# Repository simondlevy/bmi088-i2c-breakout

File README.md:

# BMI088 I^2 Breakout
Tiny I<sup>2</sup>C breakout board for the Bosch BMI088 Inertial Measurement Unit.  Available at tindie.com in 
[standard through-hole](https://www.tindie.com/products/bobbiebots/bmi088-i2c-breakout/) and 
[castellated](https://www.tindie.com/products/bobbiebots/bmi088-i2c-breakout-castellated-pin-version/) versions.

Arduino library [here](https://github.com/simondlevy/bmi088-arduino).

Based on https://github.com/AeroStrike/BMI088-Breakout-Board.

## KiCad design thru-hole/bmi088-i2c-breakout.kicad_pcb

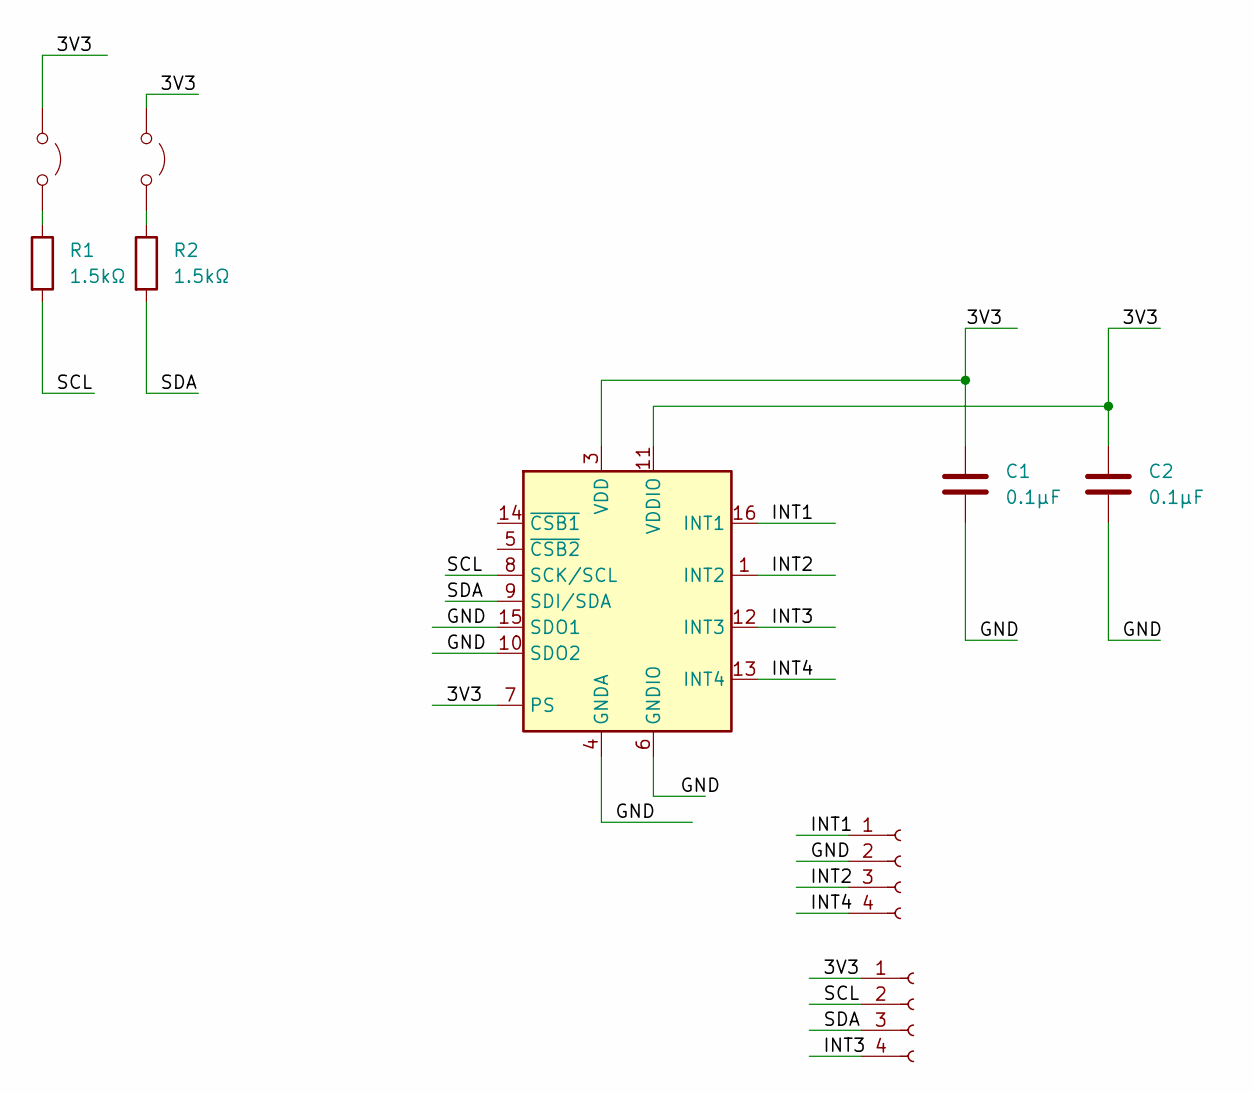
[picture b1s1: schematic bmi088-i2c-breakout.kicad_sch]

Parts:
C1, C2: 0.1μF; C_0201_0603Metric
J1, J2: Conn_01x04_Socket; PinHeader_1x04_P2.54mm_Vertical
JP1: Jumper_1_Open; C_0201_0603Metric
JP2: Jumper_2_Open; C_0201_0603Metric
R1, R2: 1.5kΩ; R_0201_0603Metric
U1: BMI088; Bosch_LGA-16_4.5x3mm_P0.5mm_LayoutBorder7x1y_ClockwisePinNu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

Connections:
/3V3: C1.1, C2.1, J1.1, JP1.1 (A), JP2.1 (A), U1.3 (VDD), U1.7 (PS), U1.11 (VDDIO)
/GND: C1.2, C2.2, J2.2, U1.2 (GNDA), U1.4 (GNDA), U1.6 (GNDIO), U1.10 (SDO2), U1.15 (SDO1)
/INT1: J2.1, U1.16 (INT1)
/INT2: J2.3, U1.1 (INT2)
/INT3: J1.4, U1.12 (INT3)
/INT4: J2.4, U1.13 (INT4)
/SCL: J1.2, R1.2, U1.8 (SCK/SCL)
/SDA: J1.3, R2.2, U1.9 (SDI/SDA)
unnamed: JP1.2 (B), R1.1
unnamed: JP2.2 (B), R2.1

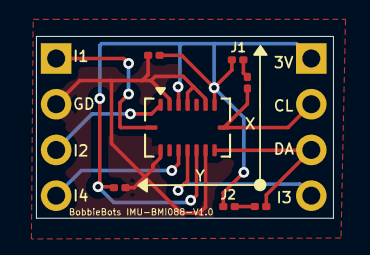
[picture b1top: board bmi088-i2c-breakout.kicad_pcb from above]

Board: 2 copper layers, 16.5 x 10.1 mm, 9 parts (0 on the bottom side), 10 nets.

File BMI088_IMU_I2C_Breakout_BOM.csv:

Comment,Designator,Footprint
,,
0.1uF,"C1, C2",CL10B104KB8NNWC 0.1uF 0603
1.5K Ohm,"R1, R2",WR06X152 JTL 1.5K Ohm 0603
BMI088,U1,BMI088 IMU

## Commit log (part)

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2026-06-08 new file: bmi088-i2c-breakout.kicad_pro
2026-06-08 modified: README.md
2026-06-08 modified: bmi088-i2c-breakout.kicad_pcb
2026-06-09 new file: BMI088_IMU_I2C_Breakout_BOM.csv
2026-06-10 Fixed mis-labeled resistors
2026-06-10 deleted: BMI088_IMU_I2C_Breakout_BOM.csv
2026-06-20 renamed: bmi088-i2c-breakout.kicad_pcb -> castellated/bmi088-i2c-breakout.kicad_pcb
2026-06-20 modified: thru-hole/bmi088-i2c-breakout.kicad_pcb
